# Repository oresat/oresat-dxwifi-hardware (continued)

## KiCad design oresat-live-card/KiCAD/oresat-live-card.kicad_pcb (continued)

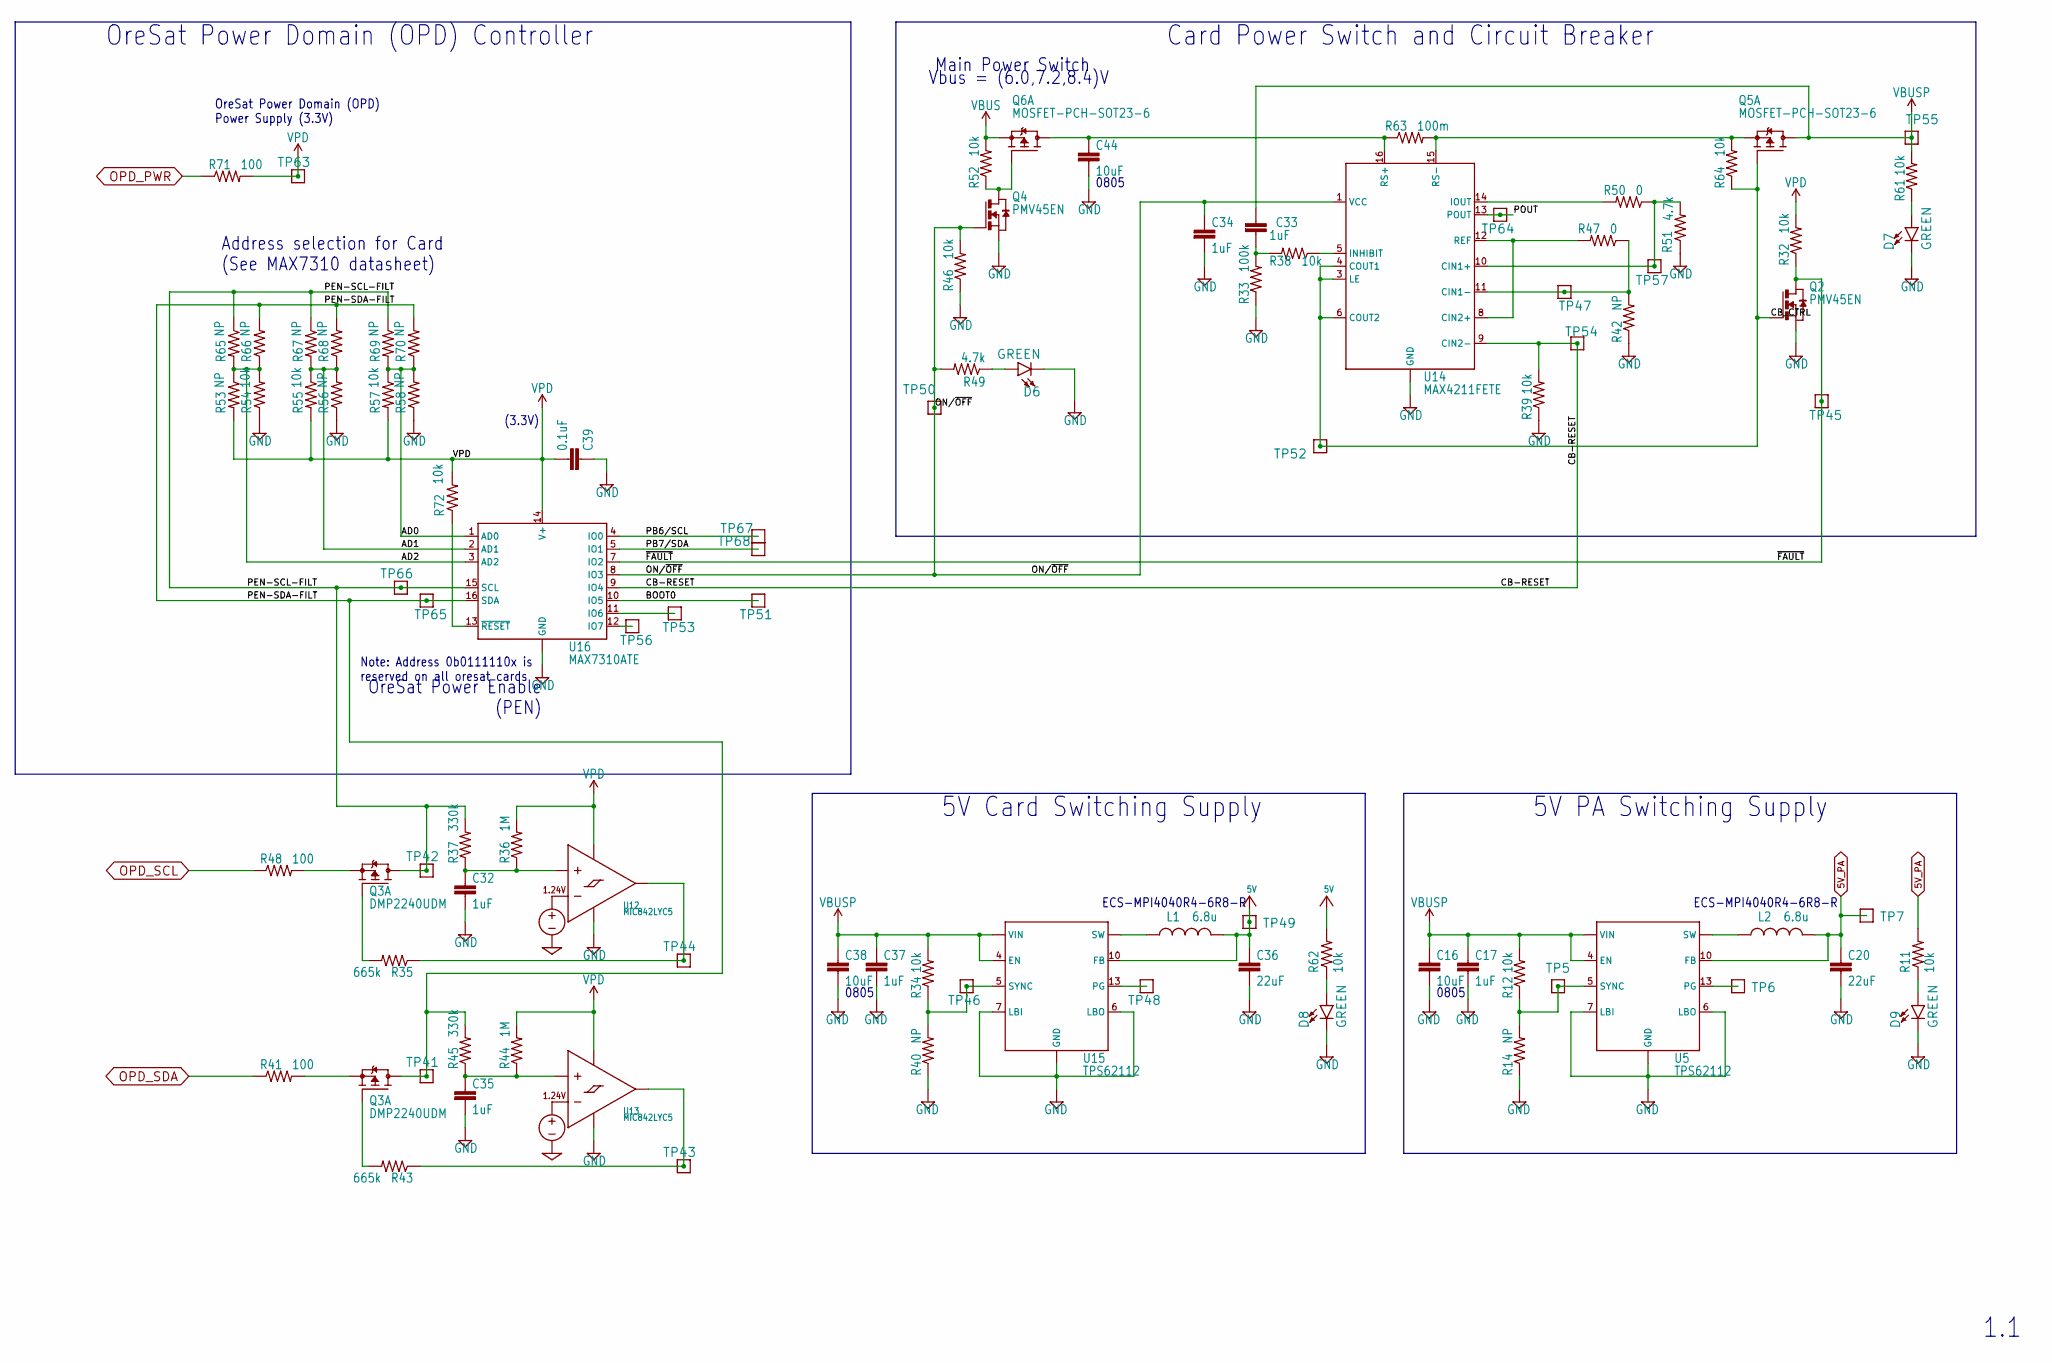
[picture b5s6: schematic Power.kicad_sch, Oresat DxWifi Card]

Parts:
C16, C38, C44: 10uF; .0805-B
C17, C34, C37: 1uF; .0603-A
C20: GCJ32ER71C226KE01L; C1210
C32, C35: 1uF; .0805-B-NOSILK
C33: CL05B104KO5NNNC; .0603-A
C36: 22uF; C1210
C39: 0.1uF; .0603-A
D6, D7, D8, D9: 150060VS55040; LED-0603
L1, L2: 6.8u; ECS-MPI4040
Q2, Q4: PMV45EN2R; SOT23
Q3: DMP2240UDM; SOT23-6
Q5, Q6: DMP3050LVT-7; SOT23-6
R11, R12, R32, R34, R39, R46, R52, R61, R62, R64, R72: 10k; .0603-A
R14, R33, R38, R40, R42, R51, R53, R54, R55, R56, R57, R58, R65, R66, R67, R68, R69, R70: RC1005F6653CS; .0603-A
R35, R43: 665k; .0603-A
R36, R44: 1M; .0603-A
R37, R45: 330k; .0603-A
R41, R48, R71: 100; .0603-A
R47, R50: 0; .0603-A
R49: 4.7k; .0603-A
R63: 100m; R1206
TP5, TP6, TP7, TP41, TP42, TP43, TP44, TP45, TP46, TP47, TP48, TP49, TP50, TP51, TP52, TP53, TP54, TP55, TP56, TP57, TP63, TP64, TP65, TP66, TP67, TP68: TEST-POINT; 2MM-TEST-POINT
U5, U15: TPS62112; S-PVQFN-16
U12, U13: MIC842LYC5; SC70-5
U14: MAX4211FETE; QFN65P400X400X80-17T210
U16: MAX7310ATE; QFN65P400X400X80-17T210

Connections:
5V: C36.1, L1.2, R62.2, TP49.1, U15.10 (FB); also elsewhere on the board
5V_PA: C20.1, L2.2, R11.2, TP7.1, U5.10 (FB); also elsewhere on the board
/Power/AD0: R57.1, R58.2, R69.2, R70.1, U16.1 (AD0)
/Power/AD1: R55.1, R56.2, R67.2, R68.1, U16.2 (AD1)
/Power/AD2: R53.1, R54.2, R65.2, R66.1, U16.3 (AD2)
/Power/BOOT0: TP51.1, U16.10 (IO5)
/Power/CB-RESET: R39.2, TP54.1, U14.9 (CIN2-), U16.9 (IO4)
/Power/CB_CTRL: Q2.1 (G), Q5.1 (G), R64.1, TP52.1, U14.3 (LE), U14.4 (COUT1), U14.6 (COUT2)
/Power/ON/~OFF: C34.1, Q4.1 (G), R46.2, R49.2, TP50.1, U14.1 (VCC), U16.8 (IO3)
/Power/PB6/SCL: TP67.1, U16.4 (IO0)
/Power/PB7/SDA: TP68.1, U16.5 (IO1)
/Power/POUT: TP64.1, U14.13 (POUT)
/Power/~FAULT: Q2.3 (D), R32.1, TP45.1, U16.7 (IO2)
unnamed: C32.1, R36.1, R37.1, U12.1 (INP)
unnamed: C33.1, R33.2, R38.2
unnamed: C35.1, R44.1, R45.1, U13.1 (INP)
unnamed: C44.1, Q6.6 (D), R63.1, U14.16 (RS+)
unnamed: D6.A, R49.1
unnamed: D7.A, R61.1
unnamed: D8.A, R62.1
unnamed: D9.A, R11.1
unnamed: L1.1, U15.14 (SW), U15.15 (SW)
unnamed: L2.1, U5.14 (SW), U5.15 (SW)
unnamed: Q4.3 (D), Q6.1 (G), R52.1
unnamed: Q5.5 (S), R63.2, R64.2, U14.15 (RS-)
unnamed: R12.1, R14.2, TP5.1, U5.5 (SYNC)
unnamed: R34.1, R40.2, TP46.1, U15.5 (SYNC)
unnamed: R35.1, TP44.1, U12.4 (OUT)
unnamed: R38.1, U14.5 (INHIBIT)
unnamed: R42.2, R47.1, TP47.1, U14.11 (CIN1-)
unnamed: R43.1, TP43.1, U13.4 (OUT)
unnamed: R47.2, U14.8 (CIN2+), U14.12 (REF)
unnamed: R50.1, R51.2, TP57.1, U14.10 (CIN1+)
unnamed: R50.2, U14.14 (IOUT)
unnamed: R72.1, U16.13 (~RESET)
unnamed: TP6.1, U5.13 (PG)
unnamed: TP48.1, U15.13 (PG)
unnamed: TP53.1, U16.11 (IO6)
unnamed: TP56.1, U16.12 (IO7)
OPD_PWR: R71.1; also elsewhere on the board
OPD_SCL: R48.1; also elsewhere on the board
OPD_SDA: R41.1; also elsewhere on the board
VBUS: Q6.5 (S), R52.2; also elsewhere on the board
VBUSP: C16.1, C17.1, C33.2, C37.1, C38.1, Q5.6 (D), R12.2, R34.2, R61.2, TP55.1, U5.2 (VIN), U5.3 (VIN), U5.4 (EN), U5.8 (VIN), U15.2 (VIN), U15.3 (VIN), U15.4 (EN), U15.8 (VIN)
VPD: C39.2, R32.2, R36.2, R44.2, R53.2, R55.2, R57.2, R71.2, R72.2, TP63.1, U12.5 (VDD), U13.5 (VDD), U16.14 (V+)

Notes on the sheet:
0805
5V PA Switching Supply
ECS-MPI4040R4-6R8-R
1.1
OreSat Power Enable (PEN)
Card Power Switch and Circuit Breaker
(3.3V)
Address selection for Card (See MAX7310 datasheet)
OreSat Power Domain (OPD) Power Supply (3.3V)
Vbus = (6.0,7.2,8.4)V
OreSat Power Domain (OPD) Controller
5V Card Switching Supply
Main Power Switch
Note: Address 0b0111110x is reserved on all oresat cards

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
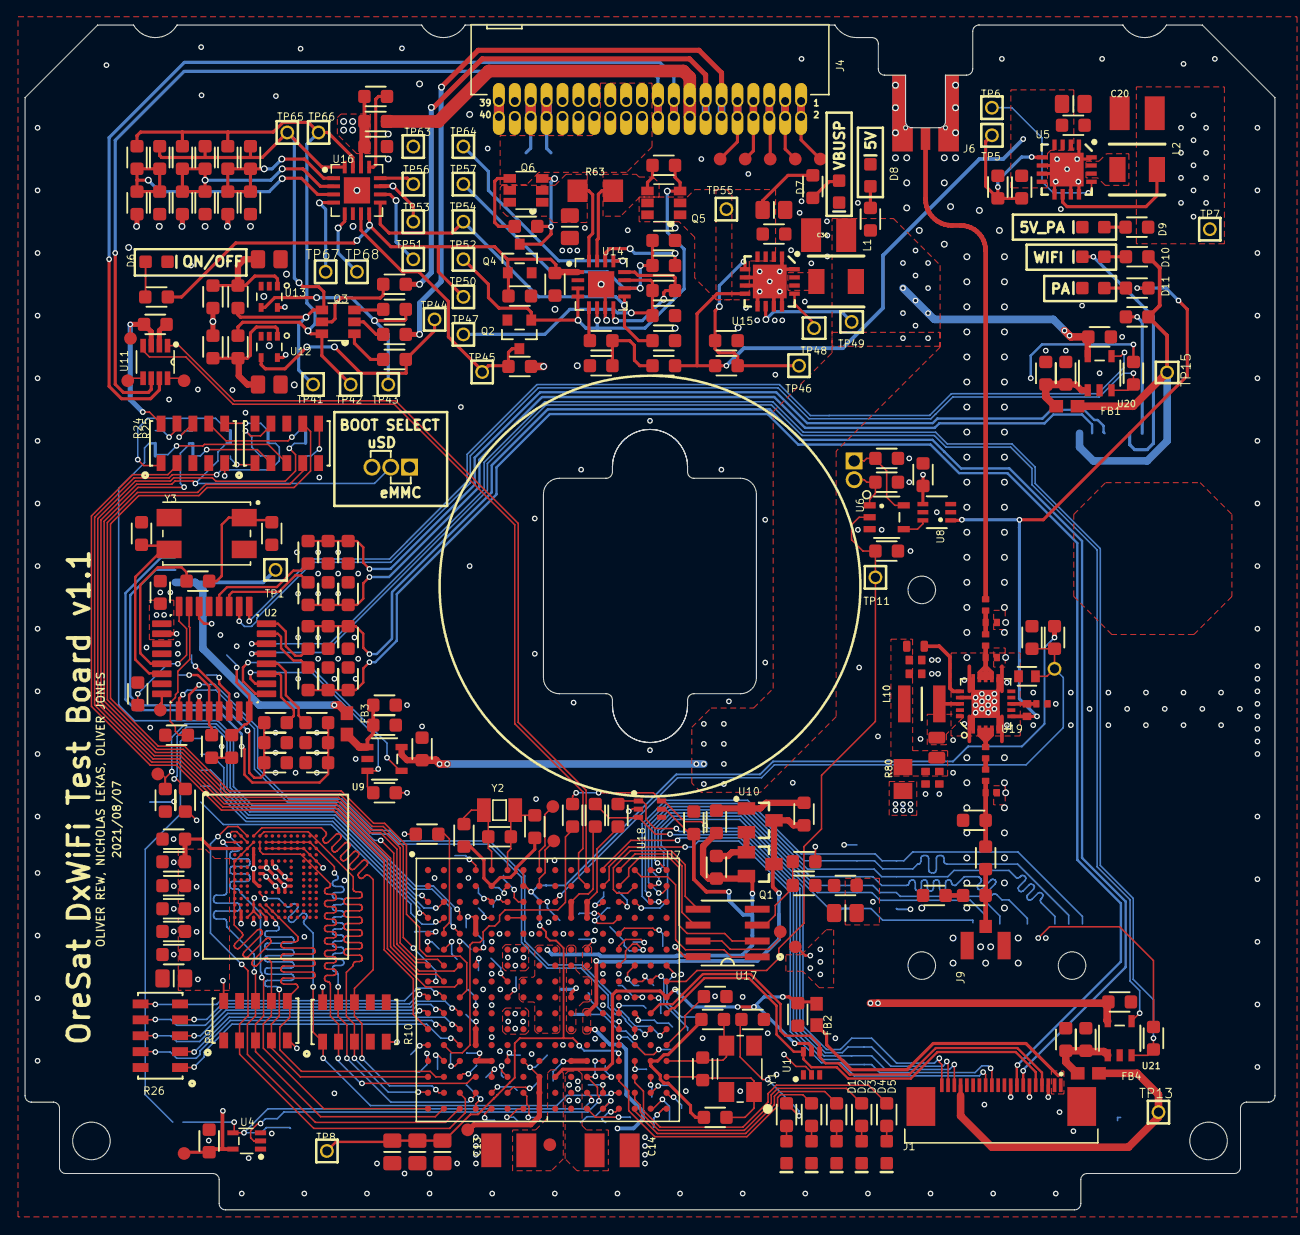
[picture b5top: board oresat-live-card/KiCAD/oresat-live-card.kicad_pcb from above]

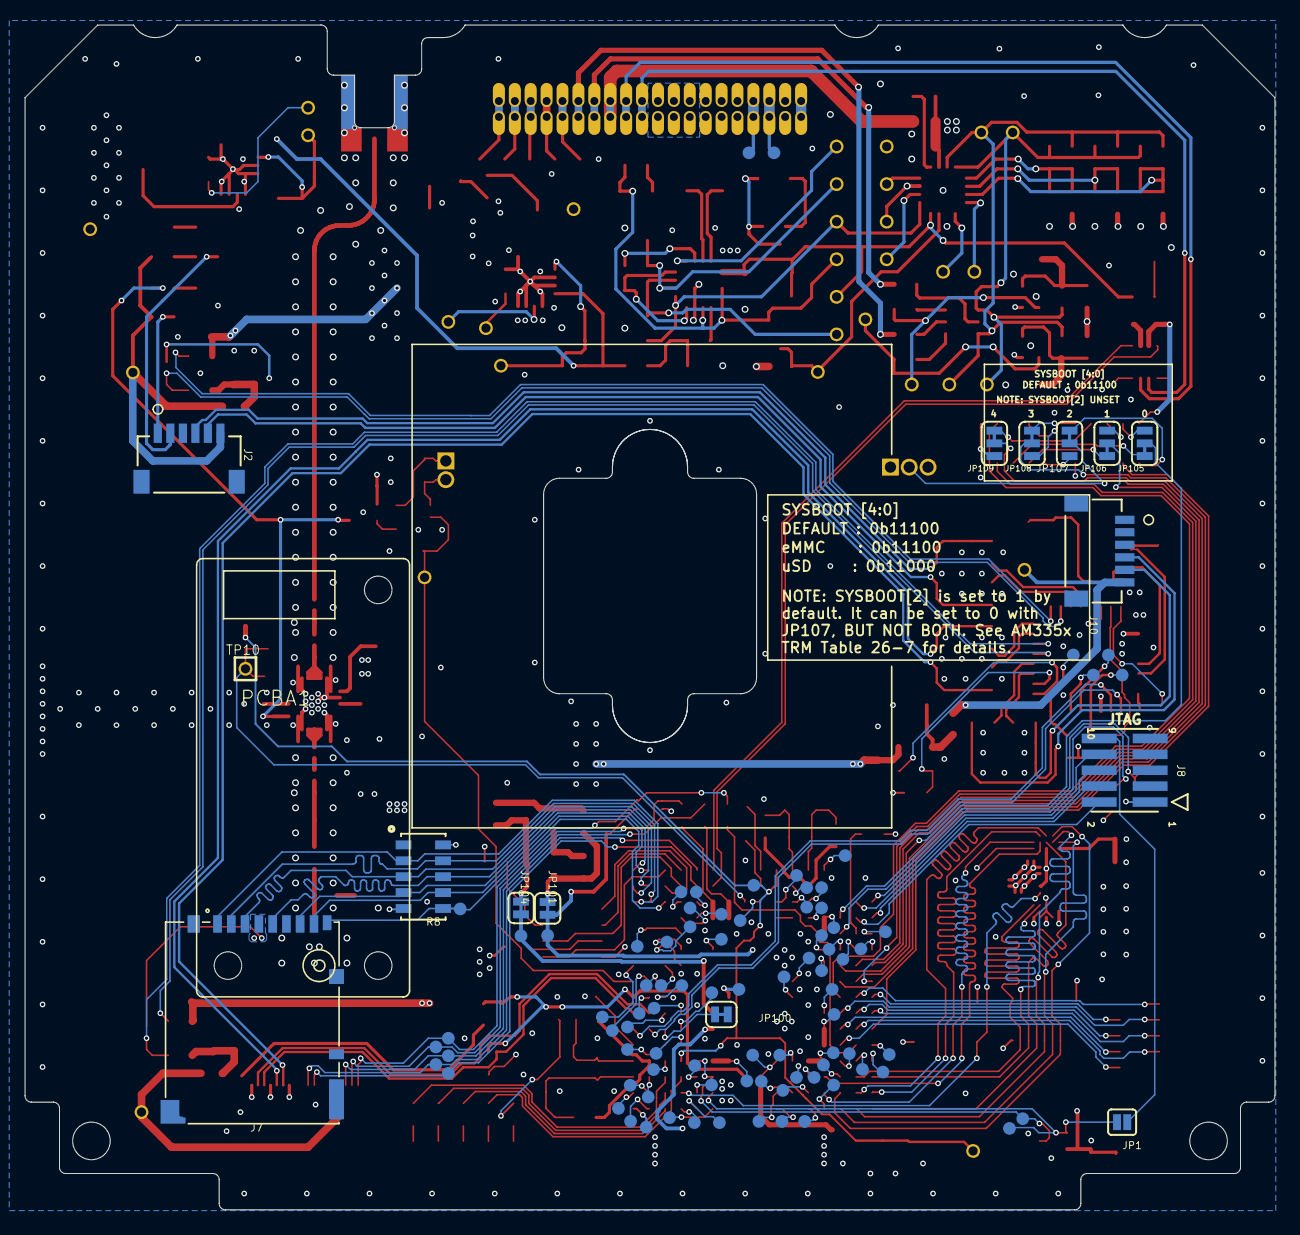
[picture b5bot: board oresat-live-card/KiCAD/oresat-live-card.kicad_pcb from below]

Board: 4 copper layers, 99.8 x 94.6 mm, 371 parts (99 on the bottom side), 292 nets.

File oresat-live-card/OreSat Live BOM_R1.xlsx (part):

Part | Qty per board | Extended Qty | Extras | Qty Needed | Qty on Hand | Qty to Order | Value | Package | MFR | MPN | Alt MFR | Alt MPN | DESCRIPTION
C1, C2, C7, C8, C16, C38, C44 | 7 | 28 | 2 | 30 | 9 | 20 | 10uF | .0805-B | TDK Corporation | CGA4J1X7S1C106M125AE |  | CGA4J1X7S1C106K125AE | CAP CER 10UF 16V X7S 0805
C13, C14, C20, C36 | 4 | 16 | 4 | 20 | 15 | 5 | 22uF | C1210 | TDK Corporation | CGA6P1X7R1C226M250AC |  |  | CAP CER 22UF 16V X7R 1210
C19, C22, C29, C30 | 4 | 16 | 4 | 20 | 8 | 10 | 12pF | .0603-A | TDK Corporation | CGA3E2C0G1H120J080AA |  |  | CAP CER 12PF 50V C0G 0603
C24, C25 | 2 | 8 | 2 | 10 | 4 | 10 | 1000PF | .0805-B | TDK Corporation | CGA4F2X7R2A102K085AE |  |  | CAP CER 1000PF 100V X7R 0805
C26 | 1 | 4 | 6 | 10 | 7 | 0 | 0.1uF | .0805-B | TDK Corporation | CGA4J2X7R1H104K125AE |  |  | CAP CER 0.1UF 50V X7R 0805
C3, C5, C6, C9, C10, C12, C17, C33, C34, C37 | 10 | 40 | 10 | 50 | 20 | 30 | 1uF | .0603-A | TDK Corporation | CGA3E1X7R1C105K080AC |  |  | CAP CER 1UF 16V X7R 0603
C32, C35 | 2 | 8 | 2 | 10 | 4 | 10 | 1uF | .0805-B-NOSILK | TDK Corporation | CGA4J2X7R1C105K125AA |  |  | CAP CER 1UF 16V X7R 0805
C4, C11, C15, C18, C21, C23, C31, C39, C40, C41 | 10 | 40 | 10 | 50 | 17 | 30 | 0.1uF | .0603-A | TDK Corporation | CGA3E2X7R1E104K080AA |  |  | CAP CER 0.1UF 25V X7R 0603
C43, C45, C46, C47 | 4 | 16 | 4 | 20 | 8 | 10 | 0.1uF | .0402-B-NOSILK | TDK Corporation | CGA2B1X7R1C104K050BC |  |  | CAP CER 0.1UF 16V X7R 0402
C48 | 1 | 4 | 6 | 10 | 14 | 0 | 1000pF | .0402-B-NOSILK | TDK Corporation | CGA2B2NP01H102J050BA |  |  | CAP CER 1000PF 50V NP0 0402
C49 | 1 | 4 | 6 | 10 | 25 | 0 | 100pF | .0402-C-NOSILK | Murata | GCM1555C1H101GA16D |  |  | CAP CER 100PF 50V C0G/NP0 0402
C50 | 1 | 4 | 6 | 10 | 3 | 10 | 3.0pF | .0402-C-NOSILK | AVX | 04025U3R0BAT2A |  |  | CAP CER 3PF 50V NP0 0402
C51 | 1 | 4 | 6 | 10 | 1 | 10 | 1.1pF | .0402-C-NOSILK | AVX | 04025J1R1PBSTR\500 |  |  | 50V 1.1pF .02pFTol ThinFilm 0402
C51a | 1 | 4 | 6 | 10 | 1 | 10 | 1.4pF | .0402-C-NOSILK | AVX | 04025J1R4PBSTR\500 |  |  | 50V 1.4pF .02pFTol ThinFilm 0402
C52 | 1 | 4 | 6 | 10 | 3 | 10 | 1.6pF | .0402-C-NOSILK | AVX | 04025U1R6BAT2A |  |  | CAP CER 1.6PF 50V NP0 0402
D1, D7, D8 | 3 | 12 | 3 | 15 | 5 | 10 | GREEN | LED-0603 | Würth Elektronik | 150060GS75020 |  |  | Green 525nm LED 3.2V 0603
D2, D3, D4, D5 | 4 | 16 | 4 | 20 | 8 | 10 | BLUE | LED-0603 | Würth Elektronik | 150060BS75020 |  |  | Blue 470nm LED 3.2V 0603
D6 | 1 | 4 | 6 | 10 | 10 | 0 | GREEN | LED-0603 | Würth Elektronik | 150060VS55040 |  |  | Green 573nm LED 2V 0603
D9, D10 | 2 | 8 | 2 | 10 | 1 | 10 | GREEN | LED-0603 | Lite-On Inc. | LTST-C193KGKT-5A |  |  | Green 572nm LED 2V 0603
D11 | 1 | 4 | 6 | 10 | 8 | 0 | RED | LED-0603 | Lite-On Inc. | LTST-C193KRKT-5A |  |  | Red 631nm LED 2V 0603
FB1, FB2 | 2 | 8 | 2 | 10 | 4 | 10 | 30Ω/1.8A | 0603 | Murata Electronics | BLM18KG300JH1D |  |  | FERRITE BEAD 30 OHM 0603 1 LN
J1 | 1 | 4 | 1 | 5 | 3 | 2 | ORESAT-DEBUG-CONNECTOR-CARD | TE_2-1734592-0 | TE Connectivity AMP Connectors | 2-1734592-0 |  |  | CONN FPC BOTTOM 20POS 0.50MM R/A
J2 | 1 | 4 | 1 | 5 | 3 | 2 | SM06B-SRSS-TB(LF)(SN) | CONN_SM06B-SRSS-TB_JST | JST Sales America Inc. | SM06B-SRSS-TB(LF)(SN) |  |  | CONN HEADER SMD R/A 6POS 1MM
J4 | 1 | 4 | 1 | 5 | 0 | 5 | TFM-120-01-L-D-RA | J-SAMTEC-TFM-120-X1-XXX-D-RA | Samtec Inc. | TFM-120-01-L-D-RA |  |  | CONN HEADER R/A 40POS 1.27MM
J6 | 1 | 4 | 1 | 5 | 5 | 0 | J-MOLEX-SMPM-73300-003X | J-MOLEX-SMPM-073300-003X | MOLEX | 0733000020 |  |  | CONN SMPM PLUG STR EDGEMNT
J7 | 1 | 4 | 1 | 5 | 2 | 3 | DM3BT-DSF-PEJS | DM3BT-DSF-PEJS | Hirose Electric Co Ltd | DM3BT-DSF-PEJS |  |  | CONN MICRO SD CARD PUSH-PUSH R/A
J9 | 1 | 4 | 1 | 5 | 3 | 2 | U.FL-R-SMA | U.FL-R-SMT | Hirose Electric Co Ltd | U.FL-R-SMT-1(10) |  |  | CONN U.FL RCPT STR 50 OHM SMD
L1,L2 | 2 | 8 | 2 | 10 | 4 | 6 | 6.8uH | ECS-MPI4040 | ECS Inc. | ECS-MPI4040R4-6R8-R |  |  | FIXED IND 6.8UH 2.4A 91 MOHM SMD
L7 | 1 | 4 | 6 | 10 | 5 | 0 | 1.7nH | .0402-C-NOSILK | Coilcraft | 0402DC-1N7XJRU |  |  | 1.7nH RF Inductor, ceramic core, 5% tol
L8 | 1 | 4 | 6 | 10 | 4 | 0 | 6.8nH | .0805-C-NOSILK | Coilcraft | 0805CS-060XJLC |  |  | Fixed Inductors 0805CS 6.8 nH 5 % 0.6 A
L9 | 1 | 4 | 6 | 10 | 13 | 0 | 1.0nH | .0402-C-NOSILK | TDK Corporation | MLK1005S1N0ST000 |  |  | FIXED IND 1NH 500MA 100 MOHM SMD
L10 | 1 | 4 | 6 | 10 | 3 | 2 | 10nH | INDC2928X203N | Coilcraft | 1008HQ-10NXJLB |  |  | Fixed Inductors 1008 10nH Unshld 5%
Q1 | 1 | 4 | 2 | 6 | 3 | 2 | MMBT2907 | SOT23-BEC | Diodes Incorporated | MMBT2907A-7-F |  |  | TRANS PNP 60V 0.6A SOT23-3
Q2, Q4 | 2 | 8 | 2 | 10 | 4 | 6 | PMV45EN | SOT23 | Nexperia USA Inc. | PMV45EN2R |  |  | MOSFET N-CH 30V 4.1A TO236AB
Q3 | 1 | 4 | 2 | 6 | 3 | 2 | DMP2240UDM | SOT23-6 | Diodes Incorporated | DMP2240UDM-7 |  |  | MOSFET 2P-CH 20V 2A SOT-26
Q5, Q6 | 2 | 8 | 2 | 10 | 4 | 6 | MOSFET-PCH-SOT23-6 | SOT23-6 | Diodes Incorporated | DMP3050LVT-7 |  |  | MOSFET P CH 30V 4.5A TSOT26
R1, R2, R3, R4, R5, R21, R30 | 7 | 28 | 4 | 32 | 11 | 20 | 1k | .0603-A | Panasonic Electronic Components | ERJ-3EKF1001V |  | ERJ-U03F1001V | RES SMD 1K OHM 1% 1/10W 0603
R11, R49, R61, R62 | 4 | 16 | 4 | 20 | 8 | 10 | 2.7k | .0603-A | Panasonic Electronic Components | ERJ-3EKF2701V |  | ERJ-U03F2701V | RES SMD 2.7K OHM 1% 1/10W 0603
R13, R36, R44 | 3 | 12 | 3 | 15 | 6 | 10 | 1M | .0603-A | Panasonic Electronic Components | ERJ-3EKF1004V |  | ERJ-U03F1004V | RES SMD 1M OHM 1% 1/10W 0603
R23 | 1 | 4 | 6 | 10 | 6 | 10 | 499 | .0603-A | Panasonic Electronic Components | ERJ-3EKF4990V |  |  | RES SMD 499 OHM 1% 1/10W 0603
R24, R25, R26 | 3 | 12 | 3 | 15 | 6 | 10 | 100K | ARRAY_EXBA-M | Panasonic Electronic Components | EXB-A10P104J |  |  | RES ARRAY 8 RES 100K OHM 2512
R29, R47, R50 | 3 | 12 | 3 | 15 | 13 | 0 | 0 | .0603-A | Panasonic Electronic Components | ERJ-3GEY0R00V |  |  | RES SMD 0 OHM JUMPER 1/10W 0603
R31 | 1 | 4 | 6 | 10 | 7 | 10 | 40.2K | .0603-A | Panasonic Electronic Components | ERJ-3EKF4022V |  |  | RES SMD 40.2K OHM 1% 1/10W 0603
R33 | 1 | 4 | 6 | 10 | 7 | 10 | 100k | .0603-A | Panasonic Electronic Components | ERJ-PA3F1003V |  |  | RES SMD 100K OHM 1% 1/4W 0603
R35, R43 | 2 | 8 | 2 | 10 | 4 | 10 | 665k | .0603-A | Panasonic Electronic Components | ERJ-3EKF6653V |  |  | RES SMD 665K OHM 1% 1/10W 0603
R37, R45 | 2 | 8 | 2 | 10 | 4 | 10 | 330k | .0603-A | Panasonic Electronic Components | ERJ-3EKF3303V |  |  | RES SMD 330K OHM 1% 1/10W 0603
R41, R48, R71, R73, R74, R75 | 6 | 24 | 4 | 28 | 10 | 20 | 100 | .0603-A | Panasonic Electronic Components | ERJ-3EKF1000V |  |  | RES SMD 100 OHM 1% 1/10W 0603
R6, R7, R12, R15, R16, R17, R18, R19, R20, R22, R28, R32, R34, R38, R39, R46, R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 | 19 | 76 | 24 | 100 | 43 | 50 | 10k | .0603-A | Panasonic Electronic Components | ERJ-3EKF1002V |  | ERJ-U03F1002V | RES SMD 10K OHM 1% 1/10W 0603
R63 | 1 | 4 | 2 | 6 | 3 | 2 | 100m | R1206 | Vishay Dale | RCWE1206R100FKEA |  |  | RES 0.1 OHM 1% 1/2W 1206
R8, R9, R10 | 3 | 12 | 3 | 15 | 9 | 6 | 10K | ARRAY_EXBA-M | Panasonic Electronic Components | EXB-A10P103J |  |  | RES ARRAY 8 RES 10K OHM 2512
R80 | 1 | 4 | 6 | 10 | 14 | 0 | 0 | R0805 | Panasonic Electronic Components | ERJ-6GEY0R00V |  |  | RES SMD 0 OHM JUMPER 1/8W 0805
R81 | 1 | 4 | 6 | 10 | 13 | 0 | 110 | .0402-B-NOSILK | Panasonic Electronic Components | ERJ-2RKF1100X |  | ERJ-U02F1100X | RES SMD 110 OHM 1% 1/10W 0402
R82 | 1 | 4 | 6 | 10 | 14 | 0 | 220 | .0603-C-NOSILK | Panasonic Electronic Components | ERJ-3EKF2200V |  | ERJ-U03F2200V | RES SMD 220 OHM 1% 1/10W 0603
R84 | 1 | 4 | 6 | 10 | 17 | 0 | 3.3 | .0402-C-NOSILK | Vishay / Dale | CRCW04023R30FKED |  |  | RES SMD 3.3 OHM 1% 1/16W 0402
R85 | 1 | 4 | 6 | 10 | 7 | 0 | 82.5 | .0603-A | Panasonic Electronic Components | ERJ-3EKF82R5V |  |  | RES SMD 82.5 OHM 1% 1/10W 0603
R86 | 1 | 4 | 6 | 10 | 7 | 0 | 93.1 | .0603-A | Panasonic Electronic Components | ERJ-3EKF93R1V |  |  | RES SMD 93.1 OHM 1% 1/10W 0603
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
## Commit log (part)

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2018-08-11 you know the drill
2018-08-11 layed out the boost converter
2018-08-12 getting close
2018-08-14 minor fixes
2018-08-29 mawr
2018-09-06 a few updates
2018-09-07 more refinements
2018-09-08 changes from design review
2018-11-15 added v1 revision notes
2019-01-30 Initial link model
    Antenna gains at 16dBi. Ground station antenna noise temperature is unknown; needs measurement. Transmitters set to 2W. Transmitter and receiver details are estimates. Modulation set to BPSK w/o FEC 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
2019-01-31 Notes fix
2019-02-01 Customized transmitters and receivers templates
2019-02-01 changed stencil openings per request
2019-02-11 This is now the hardware repo only.
2019-02-11 Better formatting, links.
2019-03-27 Added first version of the AR9271 evaluation board. No board layou yet.
2019-04-19 Most up to date board
2019-05-06 BRD and SCH now back in sync
2019-05-27 Updated link models
2019-05-28 Updated mod/demod to include FEC
2019-06-21 Updates after design review.
2019-07-15 Update UniClOGS to match handheld
2019-09-10 Update receivers and spreadsheet formatting
2019-09-11 Handheld link model formatting, minor fixes, update handheld antenna
2019-09-16 First pass of the updated AR9271 dev board. Took Stephen's fine board, and OCD'd it. Still requires stiching, better LAYER3 power layout, TNAMES cleanup, better stiching, but it's close!
2019-09-16 More stitching, polishing of power layer, no ERCs or DRCs.
2019-09-17 Rename - delete link models
2019-09-17 Rename - new link model names
2019-09-17 whoops
2019-09-18 Added holes for feet, more stitching, and DRC cleanup. DONE! SHIP IT!
2019-10-25 Added V2 board with separate TX and RX interfaces to WiFi chip
2019-11-09 Fixed silk screen based on Jeff's feedback. No change to layout, so same version.
2019-11-17 Check in for Vigely to do some modeling. All routed, but not yet polished.
2019-11-19 Cleanup, suggested by Oliver(s).
2019-12-01 Made the LNAs the correct part number.
2020-03-07 New PA test board, follows better RF practices, new input matching network, and some pointers from Qorvo.
2020-03-09 Cleaned up DRCs and stiching.
2020-03-11 Fixed filename.
2020-10-08 Added 1st draft layout for Oliver
2020-10-25 Final tweaks to the V2 after getting the V1 to work!
2021-01-13 Removed star tracker traces and added dxwifiboard.dxf
2021-01-19 placed components in proposed locations
2021-01-21 Third time is the charm? Started with Star Tracker v1.2, added new card outline, moved out all extraneaous stuff, added RF connectors.
2021-01-22 Moved components to clear the camera
2021-01-24 Routed emmc without impedance matching
2021-01-24 reverted impedance matching
2021-01-24 Routed emmc lines
2021-01-24 conected the emms to the octavo
2021-01-25 routed R26 array
2021-01-26 routed jtag and CAN transceiver uart
2021-01-26 fixed incorrect trace widths
2021-01-26 Removed unused jumpers left over from star tracker
2021-01-27 routed power for wifi
2021-01-27 Updated to tuned values, fixed BOM formatting.
2021-01-29 rerouted USB on top layer and conected it to the wifi conector
2021-01-30 got most signals off layer 15
2021-02-02 Fixed WF connector pinout
2021-02-02 Got the SD card traces off layer 15
2021-02-02 Moved OPD power indicator LEDs out of the way for RF
2021-02-03 Rearanged the front right to make more room for the WF 5v regulator
2021-02-04 routed the 5V supply for the PA and placed it on the board in a temporary spot
2021-02-04 added schematic sheet for RF
2021-02-06 Added the PA design block
2021-02-09 Moved the WiFi module to the bottom and rerouted the PA 5V regulator
2021-02-11 Added a thermister for the PA following the C3 implementation
2021-02-11 added vias to all 3.3v conections for a 3.3v pour on layer 15
2021-02-12 Added the status LED and power toggole resistor for the WiFi module
2021-02-14 chose gpio3_9 for PA_ENABLE
2021-02-15 fixed routing errors
2021-02-17 moved the PA 5V supply to the top right of the board and routed the PA TX connections
2021-02-18 routed 5V connections and cleaned up airwires and missing ground connections
2021-02-18 Removed the thermal designation from nessicary polygon pours
2021-02-19 Added 5V_PA polygon, did some OCD cleanup on RF sheet, yelled at Nick a lot.
2021-02-19 modified thermistor routing to not go though vias after it was moved
2021-02-19 Added a silkscreen identifier for the PA enable LED
2021-02-20 reworked the 5V and 3.3V polygon routing
2021-02-21 length matched the emmc data lines
2021-02-21 Added ground vias next to the RF inductors, SMPM connector, and more around the U.FL
2021-02-21 Verified all component keepout errors for adequate soldermask clerance and move a few
2021-02-21 Cleared the PA thermal path
2021-02-22 placed the silkscreen elements
2021-02-22 Added attributes to all green LEDs
2021-02-28 Added 2 more vias to the thermal path
2021-03-08 Small fixes; polishing.
2021-04-05 Updated board text to v1.1, updated flight hardware marker, fixed eMMC routed through A6 issue
2021-04-05 Moved R22 to uncover the octavo pin 1 deginator
2021-04-05 Made a small change to the RF tStop at L7
2021-04-05 Updated the OR gate and the high side PA enable footprints
2021-04-09 Adjusted misc silkscreen labels and corrected connector refdes's
2021-04-12 Replaced all test points for the PA support circuits with through hole test points
2021-04-12 changed the date on the PCB
2021-04-19 Changed TP1 on the VOUT_USB to a through hole insted of a pad
2021-04-19 Fixed the WF sourcing power from 2 sources and increased all 3.3V and 5V led resistors
2021-05-22 Added revised BOM and pdf of latest schematic
2021-08-04 added crystal for the USB hub
2021-08-04 added usb hub reset pullup and vcc filter cap
2021-08-05 Made progress on adding the USB hub and power switches
2021-08-06 replaced boot and PA_enable jumpres with smaller one, started clearing space for the usb hub
2021-08-07 added Oliver J's name and organized the ratsnest components off the board
2021-08-07 changed camera connector pinout to match wifi
2021-08-07 placed hub and usb data line componants
2021-08-07 mid way placing crystal
2021-08-08 routed data and power for host and wifi
2021-08-08 routed forgotten 5V for camera power
2021-08-08 added copper pour around adjcent 3.3v pads on the hub
2021-08-08 Made all chnges discused in 8/8 design review
2021-08-08 placed sysboot instructions and ran DRC
2021-08-09 added u.fl passthrough hole
2021-08-09 Final polish on v1.1.
    - Added pulldowns on unused USB port, added pullup on !OC input for that port.
    - Added TPL/BPL lines for the camera board and lens holder. Moved some parts around to avoid the 33.5 mm OD of the lens holder.
    - TNAMES cleanup
    - Made some traces thicker (don't use TRACE rule for wires if you can help it)
    - Fixed isolate on some layer 15 polygons
    - Cleaned up some traces coming non-orthogonally out of pads.
2021-08-15 cleaned up the schamatic and added notes for the new usb connections
2021-08-15 cleaned up most DRC errors
2021-08-15 updated BOM to include new USB hub components
2021-08-15 removed out of date schematics and BOMs
2021-08-28 started ripping things up. In the middle of condensing OPD
2021-09-04 finished ripping appart the functional chunks
2021-09-28 pulled the Octavo appart some more and placed it where I think it fits best
2022-01-30 KiCad Port of oresat live card v1.1
2022-02-27 BOM and minor cosmetic schematic updates
2022-04-30 Board updates for V1.2, more routing. Design review 1
2022-05-01 Initial import of Eagle files to KiCad
2022-05-01 re importing eagle files to kicad
2022-05-04 Deleting redundant files
2022-05-09 OreSat Live card V1.2, last silkscreen tweaks and edgecut fixes
2022-05-13 Added kicad temp files to .gitignore, and removed committed temp files.
2022-05-29 Revert "OreSatLive Card v1.2, schematic changes that I totally ment to not push last time I swear that was totally intentional"
    This reverts commit 8d63213ca5702f650b1cf534c3d24906942b58ae.
2022-05-30 Shifted C75 to be out of the way of the lens
2022-05-31 Reverted SMPM pocket drills to be outlines
2022-05-31 Fixed issue with priority level of ground plane polygon.
2022-06-17 Pushed new BOM with backup PNs, removed deprecated Eagle files, added pdf schematics
2022-07-06 Fixed schematic error with 5v regulators
2022-07-19 restoring deleted Eagle v1.1 files
2022-07-19 fixed microstrip soldermask pull keepaway
2022-07-19 fixed u.fl pad missing gnd connection
2022-07-20 cleaned up DRC errors
2022-09-18 Fixed a few DRC errors
2022-09-20 Got most of the the DRC errors, started cleaning up the warnings
2022-10-06 changes L1 and L2 to coilcraft XGL4020, grounded pin 8 of U11 for alt part compatability
2022-10-26 replaced smpm footprint, added stitching around smpm
2022-10-26 fixed more DRC errors
2022-10-29 implamented some of the changes discussed with Andrew
2022-10-31 I think this might have actully been what my last commit should have been
2022-11-03 removed weird splig ground plane
2022-11-21 generated ibom
2023-12-21 Updated OreSat Live Card. Added changes from the C3 v6 Octavo circuitry and GPS card update. Fixed some GitHub issues. Board layout still in progress.
2024-01-02 Updated silk screen and small schematic changes
2024-01-02 Fixed issue with VPD diodes
2024-01-02 Cleaned up ERC and DRC errors on DxWiFi Card
2024-05-12 Upgraded to KiCAD 8.0. Added notes on U.FL cable and USB cables to wifi and camera.
2024-07-11 Create oresat_live_receive
    Receive section for TX/RX board
2024-07-12 updated symbol paths to oresat libraries and created pcb file
2024-07-18 Created PCB and started arranging components on receive path card
2024-07-21 added DPNs to BOM
2024-08-15 simple text changes
2024-08-15 Updated board layout, traces widths, and silkscreen
2024-08-19 5V path changes and silkscreen descriptors update
2024-09-01 Updated silkscreen, grounding, and Ref Des alignment
2024-09-05 fixed connector reference designators and BOM for receive test board
2024-09-09 Added RF Tools trace
2024-09-18 refixing changes from design review
2024-09-19 added missing DPN and MPN, fixed silkscreen labels
2025-04-05 added new sheets for LNA and switching
2025-04-26 completed LNA minus pwr detect.
2025-05-03 added RF scwitches
2025-05-10 implemented notes from Oliver. Added notes for self to fix later
2025-05-23 implemented notes form Oliver J
2025-07-06 updated sheet numbering and title, merged antenna switching and tx rx switching sheets
2025-07-06 removed unused tx_rx flag
2025-08-02 Changed C118, R124, R125 from 0603 to 0402, starting layout and routing
2025-08-05 swapped placement of R105 and R88, changed R109 from 100 to 56 ohms, relabelled PWR_DET_OUT to RX_DET_OUT, added inverter to TX/RX Control switch and swapped RF1 and RF2
2025-08-23 initial routing pass completed, moved R144 and R155 to output of U6.
2025-09-17 Fixed schematic symbolrs, add notes about control logic, fixed RF path and teardrops, removed 1.1V power LED
2025-09-17 Cleaning up respository, consistent naming, and removing old cruft.
2025-09-17 Rename files to be consistent with other octavo designs.
2025-09-17 Updated OPD / power page and synced with CFC processor, fixed layout issues.
2025-09-17 Updated SIP A, B, and C. Lots of cleanup of crazy routing - this board is long in the tooth and has been rerouted several times, so there's a lot of crazy routing. Cleaning up a bit is really helping.
2025-09-21 Some changes from Oliver
2025-09-21 add GND vias near PA
2025-09-22 Moved WiFi switch to 5VA, making the entire RF subsystem powered off that one supply. Fixed up RF path, still need to remove solder mask.
2025-10-29 added Olivers BOM and footprint changes, cleaned up pcb
2025-11-02 Added f.mask to all RF traces
2025-12-23 added 100p cap to U34 CTRL line, some BOM changes
2026-05-21 Added latest BOM changes
2026-06-28 Component update
    Updated the footprint for EEPROM connector
